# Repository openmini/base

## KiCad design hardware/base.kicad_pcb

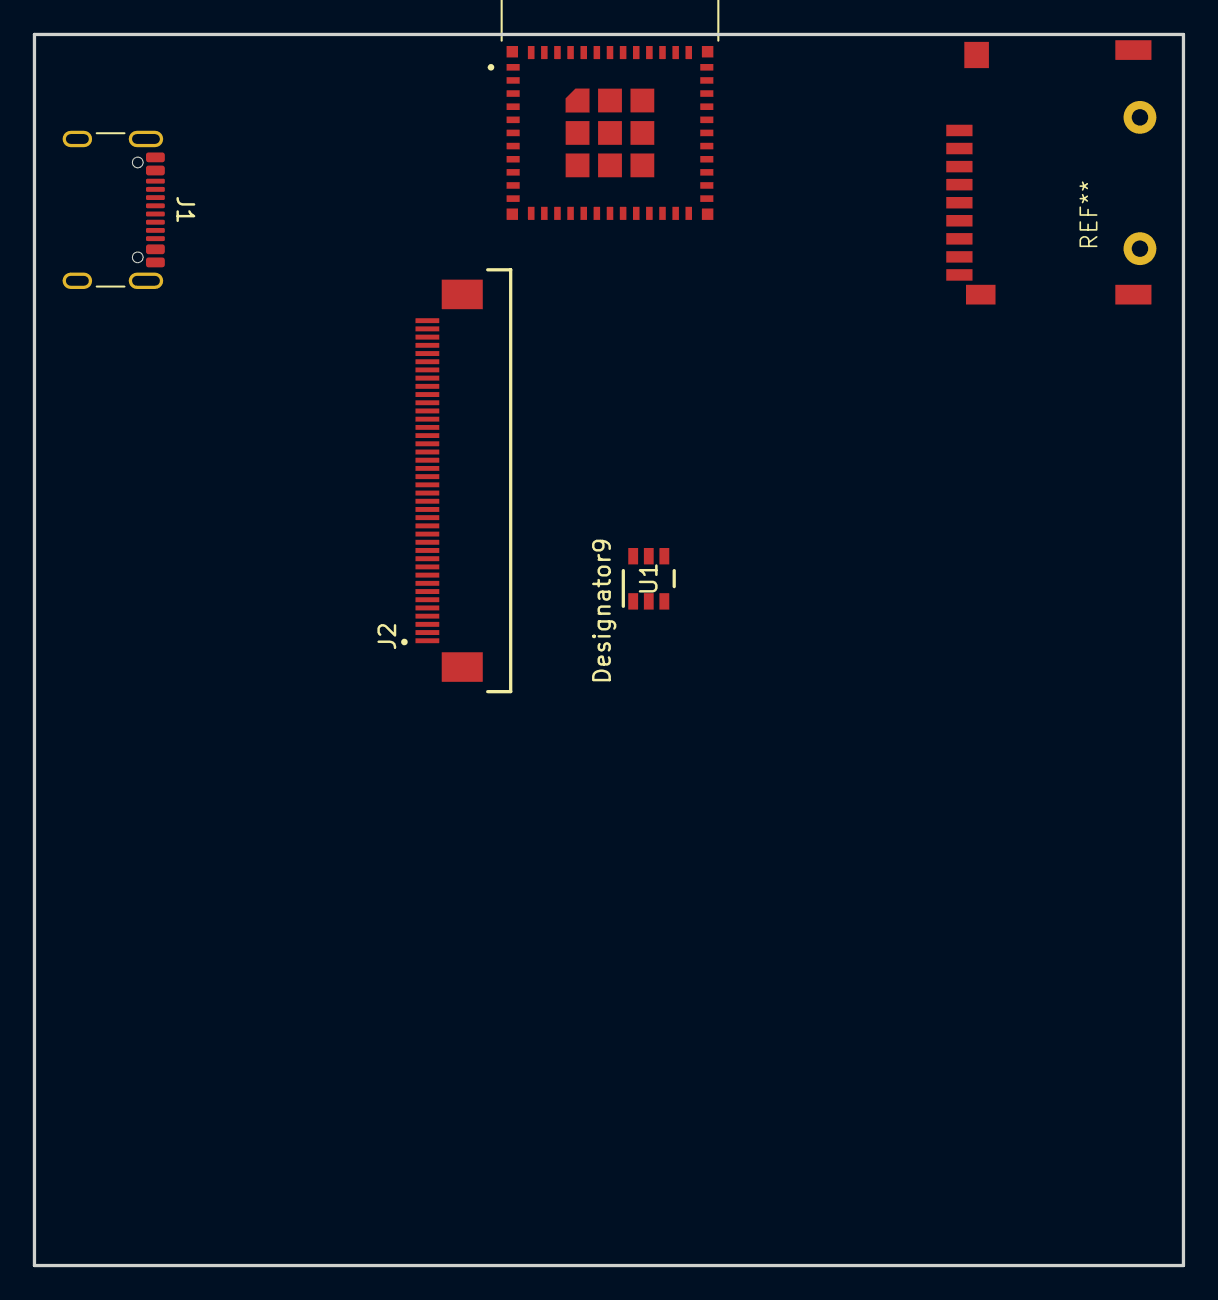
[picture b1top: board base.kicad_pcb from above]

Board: 2 copper layers, 70.0 x 75.0 mm, 3 parts (0 on the bottom side), 4 nets, no tracks yet.

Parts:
J1: USB_C_Receptacle_USB2.0_14P; USB_C_Receptacle_GCT_USB4105-xx-A_16P_TopMnt_Horizontal
J2: FFC2B21-40-T_REVA; GCT_FFC2B21-40-T_REVA
U1: BQ21040DBVR; DBV0006A_N

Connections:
unnamed: J1.A6 (D+), J1.B6 (D+)
unnamed: J1.A7 (D-), J1.B7 (D-)
unnamed: J1.A1 (GND), J1.A12 (GND), J1.B1 (GND), J1.B12 (GND)
unnamed: J1.A4 (VBUS), J1.A9 (VBUS), J1.B4 (VBUS), J1.B9 (VBUS), U1.6 (IN)

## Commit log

2024-03-11 copied pcb from opengrcalc
2024-03-19 start redesigning base implementation to better match the goals of openmini
2024-03-19 add license
2024-04-01 improved upon previous design
2024-04-07 update design files
2024-04-07 ignore backups generated by opening kicad files - this repo will soon be archived and these backups are redundant
2024-04-14 file restructuring
2024-04-14 further restructuring, improve design
2024-07-08 update blender file for rendering
